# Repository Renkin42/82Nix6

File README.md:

# 82Nix6
An open hardware Nixie Tube Internet Radio alarm clock.

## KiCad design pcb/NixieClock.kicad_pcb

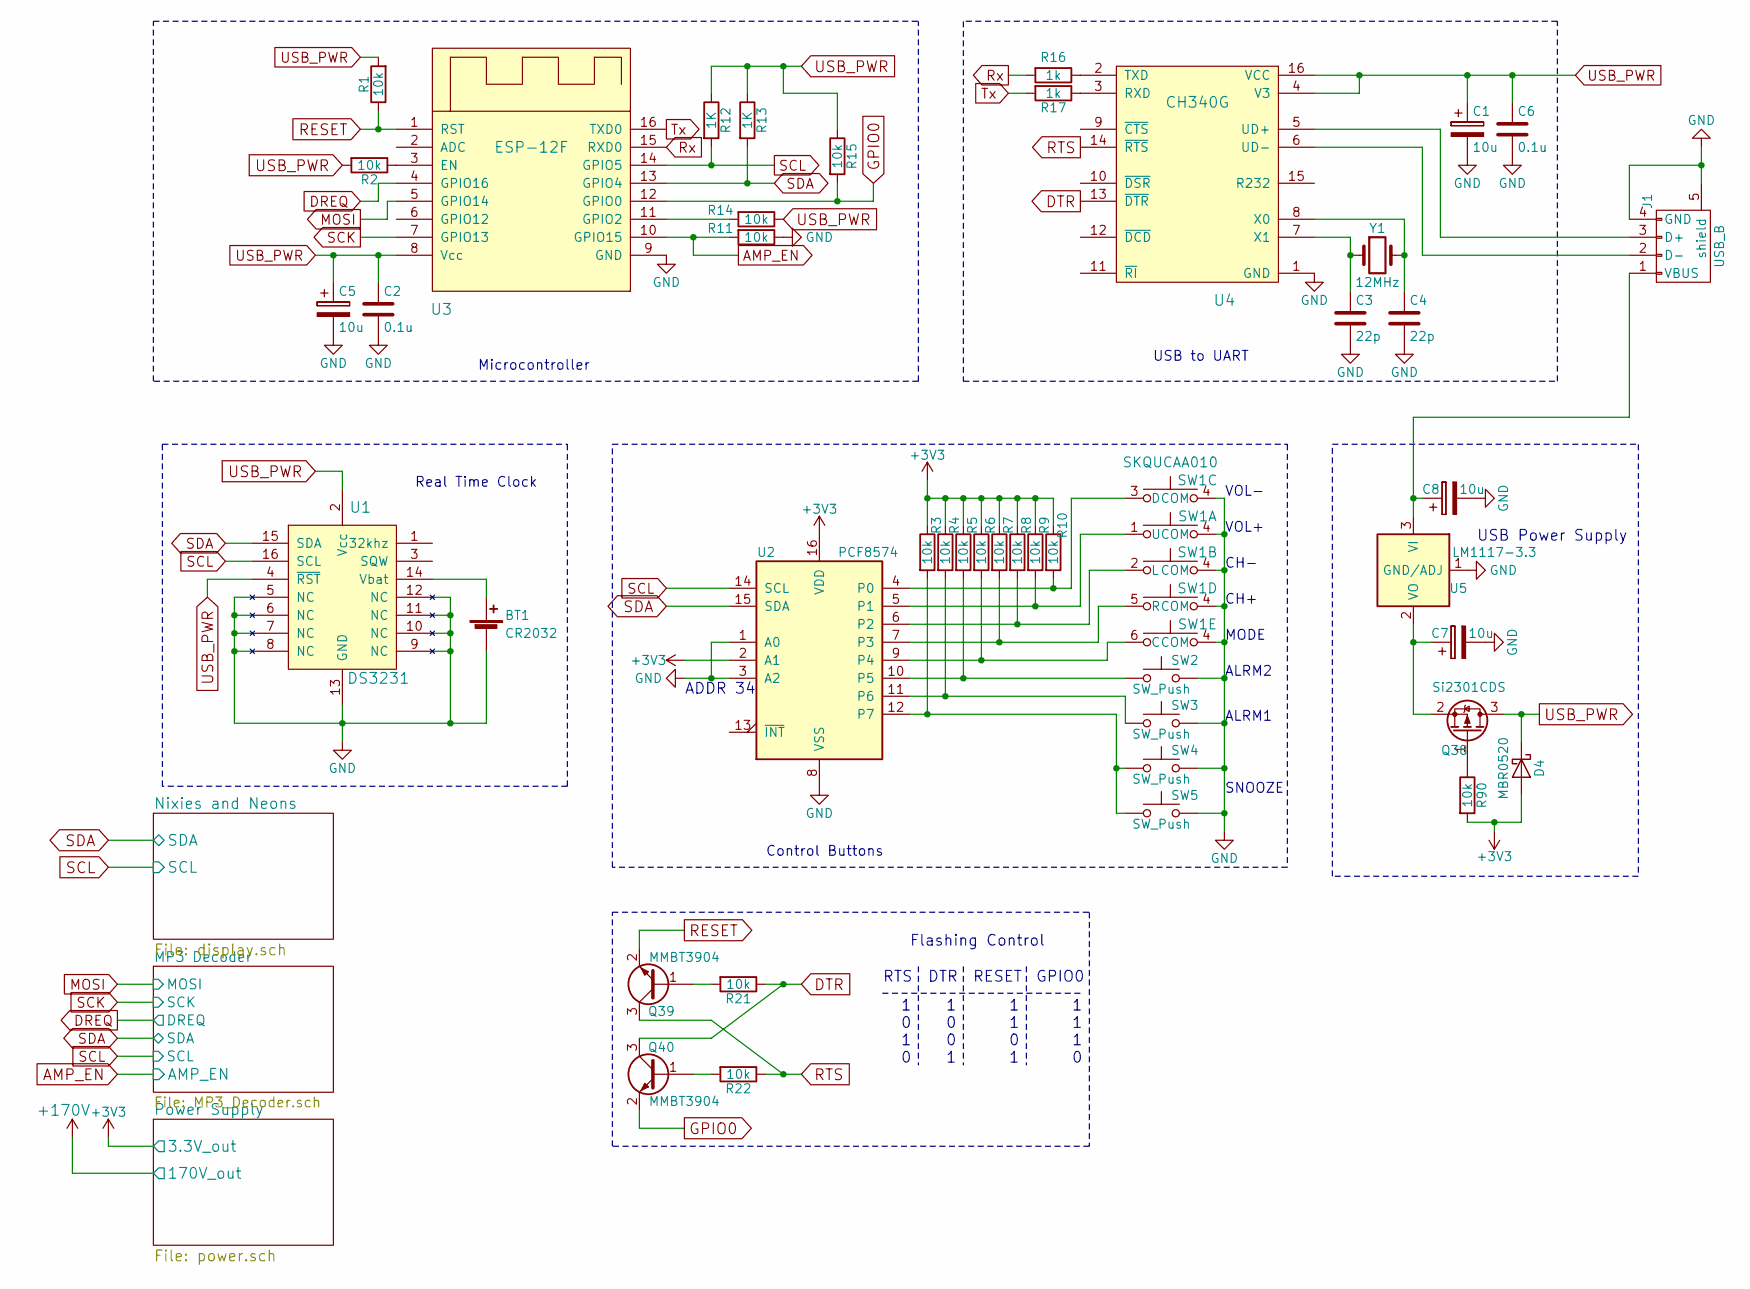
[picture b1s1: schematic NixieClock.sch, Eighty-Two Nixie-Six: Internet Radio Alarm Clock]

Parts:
BT1: CR2032; Linx_Battery_Holder
C1, C5, C7, C8: 10u; CP_Tantalum_Case-A_EIA-3216-18_Hand
C2, C6: 0.1u; C_0805_HandSoldering
C3, C4: 22p; C_0805_HandSoldering
D4: MBR0520; D_SOD-123
J1: USB_B
Q38: Si2301CDS; SOT-23_Handsoldering
Q39, Q40: MMBT3904; SOT-23_Handsoldering
R1, R2, R3, R4, R5, R6, R7, R8, R9, R10, R11, R14, R15, R21, R22, R90: 10k; R_0805_HandSoldering
R12, R13: 1K; R_0805_HandSoldering
R16, R17: 1k; R_0805_HandSoldering
SW1: SKQUCAA010
SW2, SW3: SW_Push; SW_PUSH_6mm
SW4, SW5: SW_Push; SW_Tactile_SKHH_Angled
U1: DS3231; SOIC-16W_7.5x10.3mm_Pitch1.27mm
U2: PCF8574; SOIC-16W_7.5x10.3mm_Pitch1.27mm
U3: ESP-12F; ESP_SMD_Module
U4: CH340G; SOIC-16_3.9x9.9mm_Pitch1.27mm
U5: LM1117-3.3; SOT-223
Y1: 12MHz; Crystal_HC49-4H_Vertical

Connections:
+3V3: D4.2 (A), R3.1, R4.1, R5.1, R6.1, R7.1, R8.1, R9.1, R10.1, R90.2, U2.2 (A1), U2.16 (VDD); also elsewhere on the board
AMP_EN: R11.2, U3.10 (GPIO15); also elsewhere on the board
DREQ: U3.4 (GPIO16); also elsewhere on the board
DTR: Q40.3 (C), R21.1, U4.13 (~DTR)
GND: BT1.2 (-), C1.2, C2.2, C3.2, C4.2, C5.2, C6.2, C7.2, C8.2, J1.4 (GND), J1.5 (shield), R11.1, SW1.4 (COM), SW2.2, SW3.2, SW4.2, SW5.2, U1.5 (NC), U1.6 (NC), U1.7 (NC), U1.8 (NC), U1.9 (NC), U1.10 (NC), U1.11 (NC), U1.12 (NC), U1.13 (GND), U2.1 (A0), U2.3 (A2), U2.8 (VSS), U3.9 (GND), U4.1 (GND), U5.1 (GND/ADJ); also elsewhere on the board
GPIO0: Q40.2 (E), R15.2, U3.12 (GPIO0)
MOSI: U3.5 (GPIO14); also elsewhere on the board
unnamed: BT1.1 (+), U1.14 (Vbat)
unnamed: C3.1, U4.7 (X1), Y1.1
unnamed: C4.1, U4.8 (X0), Y1.2
unnamed: C7.1, Q38.2 (S), U5.2 (VO), U5.4 (VO)
unnamed: C8.1, J1.1 (VBUS), U5.3 (VI)
unnamed: J1.2 (D-), U4.6 (UD-)
unnamed: J1.3 (D+), U4.5 (UD+)
unnamed: Q38.1 (G), R90.1
unnamed: Q39.1 (B), R21.2
unnamed: Q40.1 (B), R22.2
unnamed: R2.1, U3.3 (EN)
unnamed: R3.2, SW4.1, SW5.1, U2.12 (P7)
unnamed: R4.2, SW3.1, U2.11 (P6)
unnamed: R5.2, SW2.1, U2.10 (P5)
unnamed: R6.2, SW1.6 (C), U2.9 (P4)
unnamed: R7.2, SW1.5 (R), U2.7 (P3)
unnamed: R8.2, SW1.2 (L), U2.6 (P2)
unnamed: R9.2, SW1.1 (U), U2.5 (P1)
unnamed: R10.2, SW1.3 (D), U2.4 (P0)
unnamed: R14.2, U3.11 (GPIO2)
unnamed: R16.1, U4.2 (TXD)
unnamed: R17.1, U4.3 (RXD)
RESET: Q39.2 (E), R1.1, U3.1 (RST)
RTS: Q39.3 (C), R22.1, U4.14 (~RTS)
Rx: R16.2, U3.15 (RXD0)
SCK: U3.7 (GPIO13); also elsewhere on the board
SCL: R12.2, U1.16 (SCL), U2.14 (SCL), U3.14 (GPIO5); also elsewhere on the board
SDA: R13.2, U1.15 (SDA), U2.15 (SDA), U3.13 (GPIO4); also elsewhere on the board
Tx: R17.2, U3.16 (TXD0)
USB_PWR: C1.1, C2.1, C5.1, C6.1, D4.1 (K), Q38.3 (D), R1.2, R2.2, R12.1, R13.1, R14.1, R15.1, U1.2 (Vcc), U1.4 (~RST), U3.8 (Vcc), U4.4 (V3), U4.16 (VCC)

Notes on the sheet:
ADDR 34
Microcontroller
Control Buttons
VOL+
VOL-
CH-
CH+
MODE
ALRM1
ALRM2
SNOOZE
Real Time Clock
USB to UART
USB Power Supply
RTS
DTR
RESET
GPIO0
1 0 1 0
1 0 0 1
1 1 0 1
1 1 1 0
Flashing Control

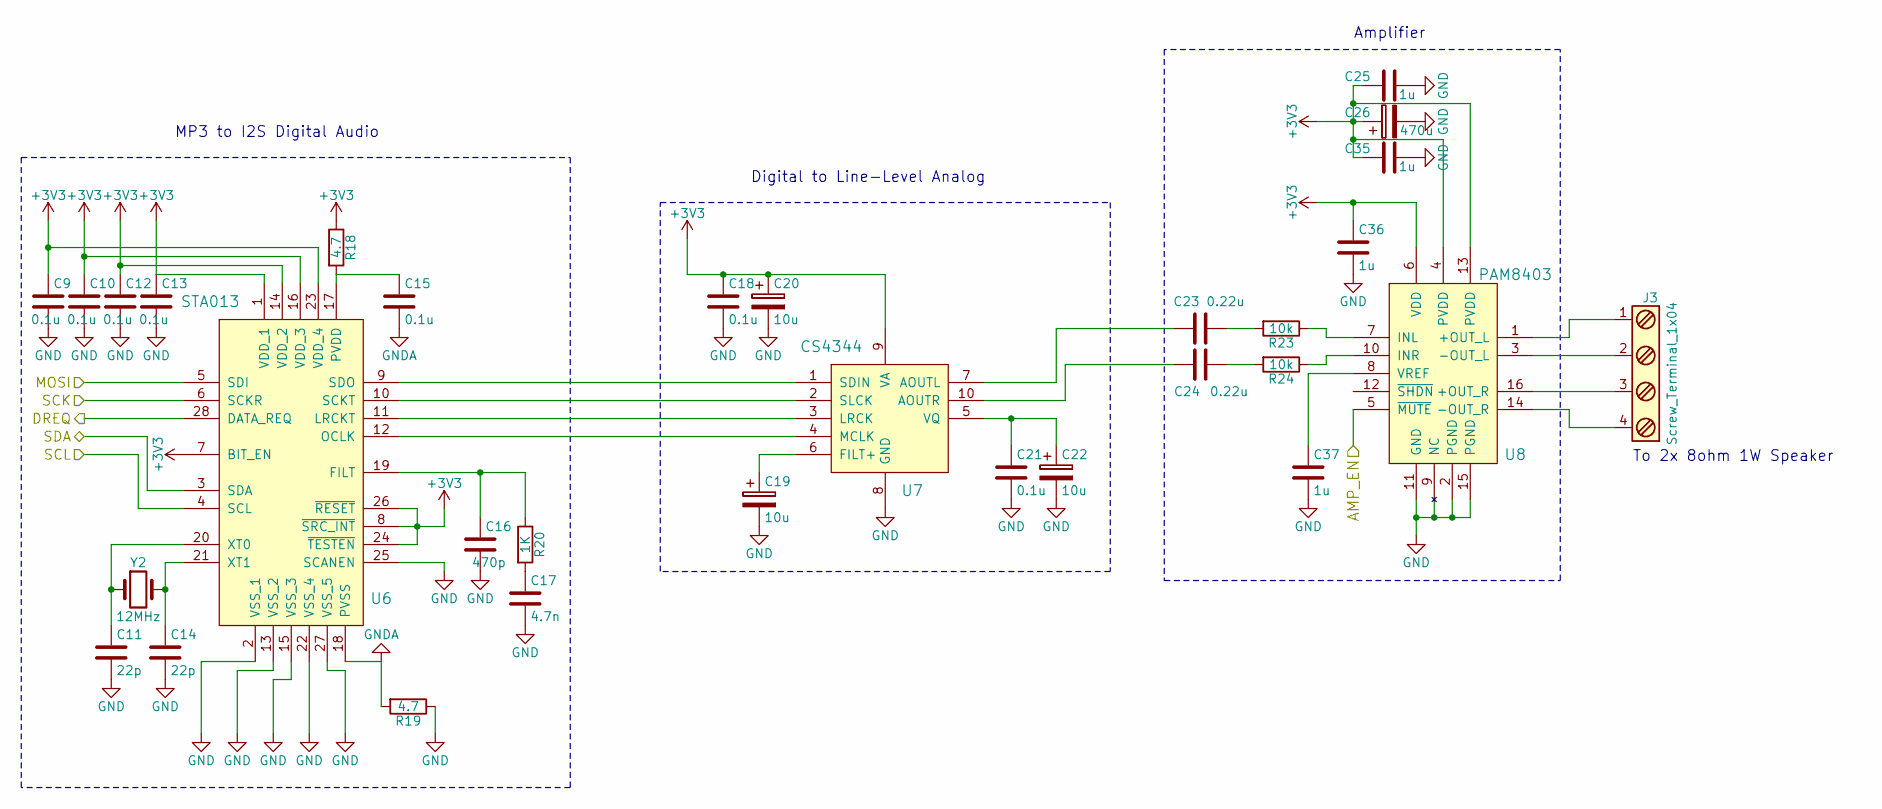
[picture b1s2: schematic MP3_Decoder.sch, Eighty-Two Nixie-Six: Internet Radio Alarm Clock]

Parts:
C9, C10, C12, C13, C15, C18, C21: 0.1u; C_0805_HandSoldering
C11, C14: 22p; C_0805_HandSoldering
C16: 470p; C_0805_HandSoldering
C17: 4.7n; C_0805_HandSoldering
C19, C20, C22: 10u; CP_Tantalum_Case-A_EIA-3216-18_Hand
C23, C24: 0.22u; C_0805_HandSoldering
C25, C35, C36, C37: 1u; C_0805_HandSoldering
C26: 470u; CP_Radial_D6.3mm_P2.50mm
J3: Screw_Terminal_1x04; TerminalBlock_Pheonix_MPT-2.54mm_4pol
R18, R19: 4.7; R_0805_HandSoldering
R20: 1K; R_0805_HandSoldering
R23, R24: 10k; R_0805_HandSoldering
U6: STA013; SOIC-28W_7.5x17.9mm_Pitch1.27mm
U7: CS4344; MSOP-10_3x3mm_Pitch0.5mm
U8: PAM8403; SOIC-16_3.9x9.9mm_Pitch1.27mm
Y2: 12MHz; Crystal_HC49-4H_Vertical

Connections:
+3V3: C9.1, C10.1, C12.1, C13.1, C18.1, C20.1, C25.1, C26.1, C35.1, C36.1, R18.1, U6.1 (VDD_1), U6.7 (BIT_EN), U6.8 (~SRC_INT), U6.14 (VDD_2), U6.16 (VDD_3), U6.23 (VDD_4), U6.24 (~TESTEN), U6.26 (~RESET), U7.9 (VA), U8.4 (PVDD), U8.6 (VDD), U8.13 (PVDD); also elsewhere on the board
AMP_EN: U8.5 (~MUTE); also elsewhere on the board
DREQ: U6.28 (DATA_REQ); also elsewhere on the board
GND: C9.2, C10.2, C11.2, C12.2, C13.2, C14.2, C16.2, C17.2, C18.2, C19.2, C20.2, C21.2, C22.2, C25.2, C26.2, C35.2, C36.2, C37.2, R19.1, U6.2 (VSS_1), U6.13 (VSS_2), U6.15 (VSS_3), U6.22 (VSS_4), U6.25 (SCANEN), U6.27 (VSS_5), U7.8 (GND), U8.2 (PGND), U8.9 (NC), U8.11 (GND), U8.15 (PGND); also elsewhere on the board
GNDA: C15.2, R19.2, U6.18 (PVSS)
MOSI: U6.5 (SDI); also elsewhere on the board
unnamed: C11.1, U6.20 (XT0), Y2.1
unnamed: C14.1, U6.21 (XT1), Y2.2
unnamed: C15.1, R18.2, U6.17 (PVDD)
unnamed: C16.1, R20.1, U6.19 (FILT)
unnamed: C17.1, R20.2
unnamed: C19.1, U7.6 (FILT+)
unnamed: C21.1, C22.1, U7.5 (VQ)
unnamed: C23.1, U7.7 (AOUTL)
unnamed: C23.2, R23.2
unnamed: C24.1, R24.2
unnamed: C24.2, U7.10 (AOUTR)
unnamed: C37.1, U8.8 (VREF)
unnamed: J3.1, U8.1 (+OUT_L)
unnamed: J3.2, U8.3 (-OUT_L)
unnamed: J3.3, U8.16 (+OUT_R)
unnamed: J3.4, U8.14 (-OUT_R)
unnamed: R23.1, U8.7 (INL)
unnamed: R24.1, U8.10 (INR)
unnamed: U6.9 (SDO), U7.1 (SDIN)
unnamed: U6.10 (SCKT), U7.2 (SLCK)
unnamed: U6.11 (LRCKT), U7.3 (LRCK)
unnamed: U6.12 (OCLK), U7.4 (MCLK)
SCK: U6.6 (SCKR); also elsewhere on the board
SCL: U6.4 (SCL); also elsewhere on the board
SDA: U6.3 (SDA); also elsewhere on the board

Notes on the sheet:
MP3 to I2S Digital Audio
Digital to Line-Level Analog
Amplifier
To 2x 8ohm 1W Speaker

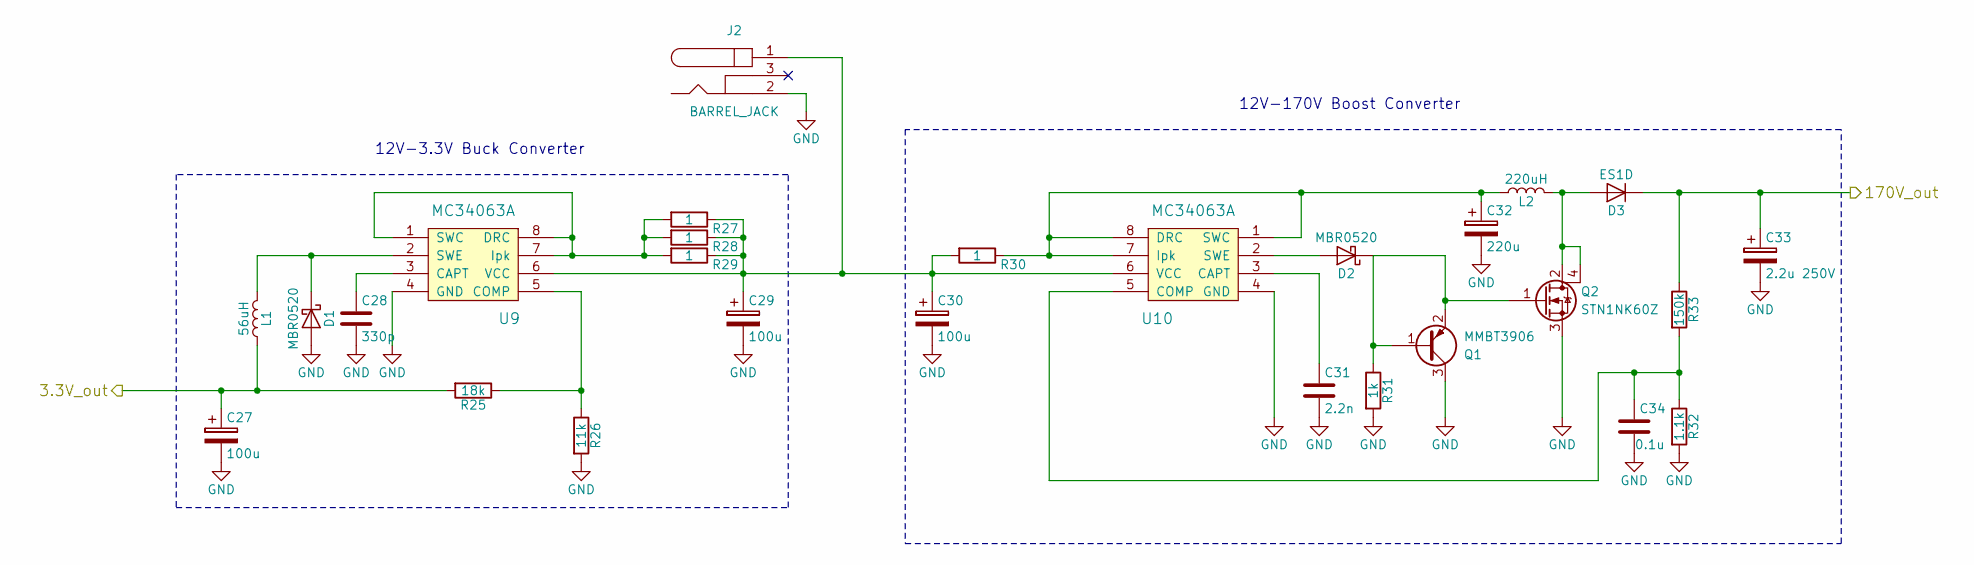
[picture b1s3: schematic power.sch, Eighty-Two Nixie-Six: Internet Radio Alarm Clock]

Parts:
C27, C29, C30: 100u; CP_Radial_D5.0mm_P2.50mm
C28: 330p; C_0805_HandSoldering
C31: 2.2n; C_0805_HandSoldering
C32: 220u; CP_Radial_D6.3mm_P2.50mm
C33: 2.2u 250V; CP_Radial_D6.3mm_P2.50mm
C34: 0.1u; C_0805_HandSoldering
D1, D2: MBR0520; D_SOD-123
D3: ES1D; D_SOD-123
J2: BARREL_JACK
L1: 56uH; Bourns_RLB9012
L2: 220uH; Bourns_RLB0914
Q1: MMBT3906; SOT-23_Handsoldering
Q2: STN1NK60Z; SOT-223
R25: 18k; R_1206_HandSoldering
R26: 11k; R_1206_HandSoldering
R27, R28, R29, R30: 1; R_0805_HandSoldering
R31: 1k; R_0805_HandSoldering
R32: 1.1k; R_1206_HandSoldering
R33: 150k; R_1206_HandSoldering
U9, U10: MC34063A; SOIC-8_3.9x4.9mm_Pitch1.27mm

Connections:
+3V3: C27.1, L1.2, R25.2; also elsewhere on the board
+170V: C33.1, D3.1 (K), R33.1; also elsewhere on the board
GND: C27.2, C28.2, C29.2, C30.2, C31.2, C32.2, C33.2, C34.2, D1.2 (A), J2.2, Q1.3 (C), Q2.3 (S), R26.2, R31.2, R32.2, U9.4 (GND), U10.4 (GND); also elsewhere on the board
unnamed: C28.1, U9.3 (CAPT)
unnamed: C29.1, C30.1, J2.1, R27.1, R28.1, R29.1, R30.2, U9.6 (VCC), U10.6 (VCC)
unnamed: C31.1, U10.3 (CAPT)
unnamed: C32.1, L2.2, R30.1, U10.1 (SWC), U10.7 (Ipk), U10.8 (DRC)
unnamed: C34.1, R32.1, R33.2, U10.5 (COMP)
unnamed: D1.1 (K), L1.1, U9.2 (SWE)
unnamed: D2.1 (K), Q1.1 (B), Q1.2 (E), Q2.1 (G), R31.1
unnamed: D2.2 (A), U10.2 (SWE)
unnamed: D3.2 (A), L2.1, Q2.2 (D), Q2.4 (D)
unnamed: R25.1, R26.1, U9.5 (COMP)
unnamed: R27.2, R28.2, R29.2, U9.1 (SWC), U9.7 (Ipk), U9.8 (DRC)

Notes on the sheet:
12V-170V Boost Converter
12V-3.3V Buck Converter

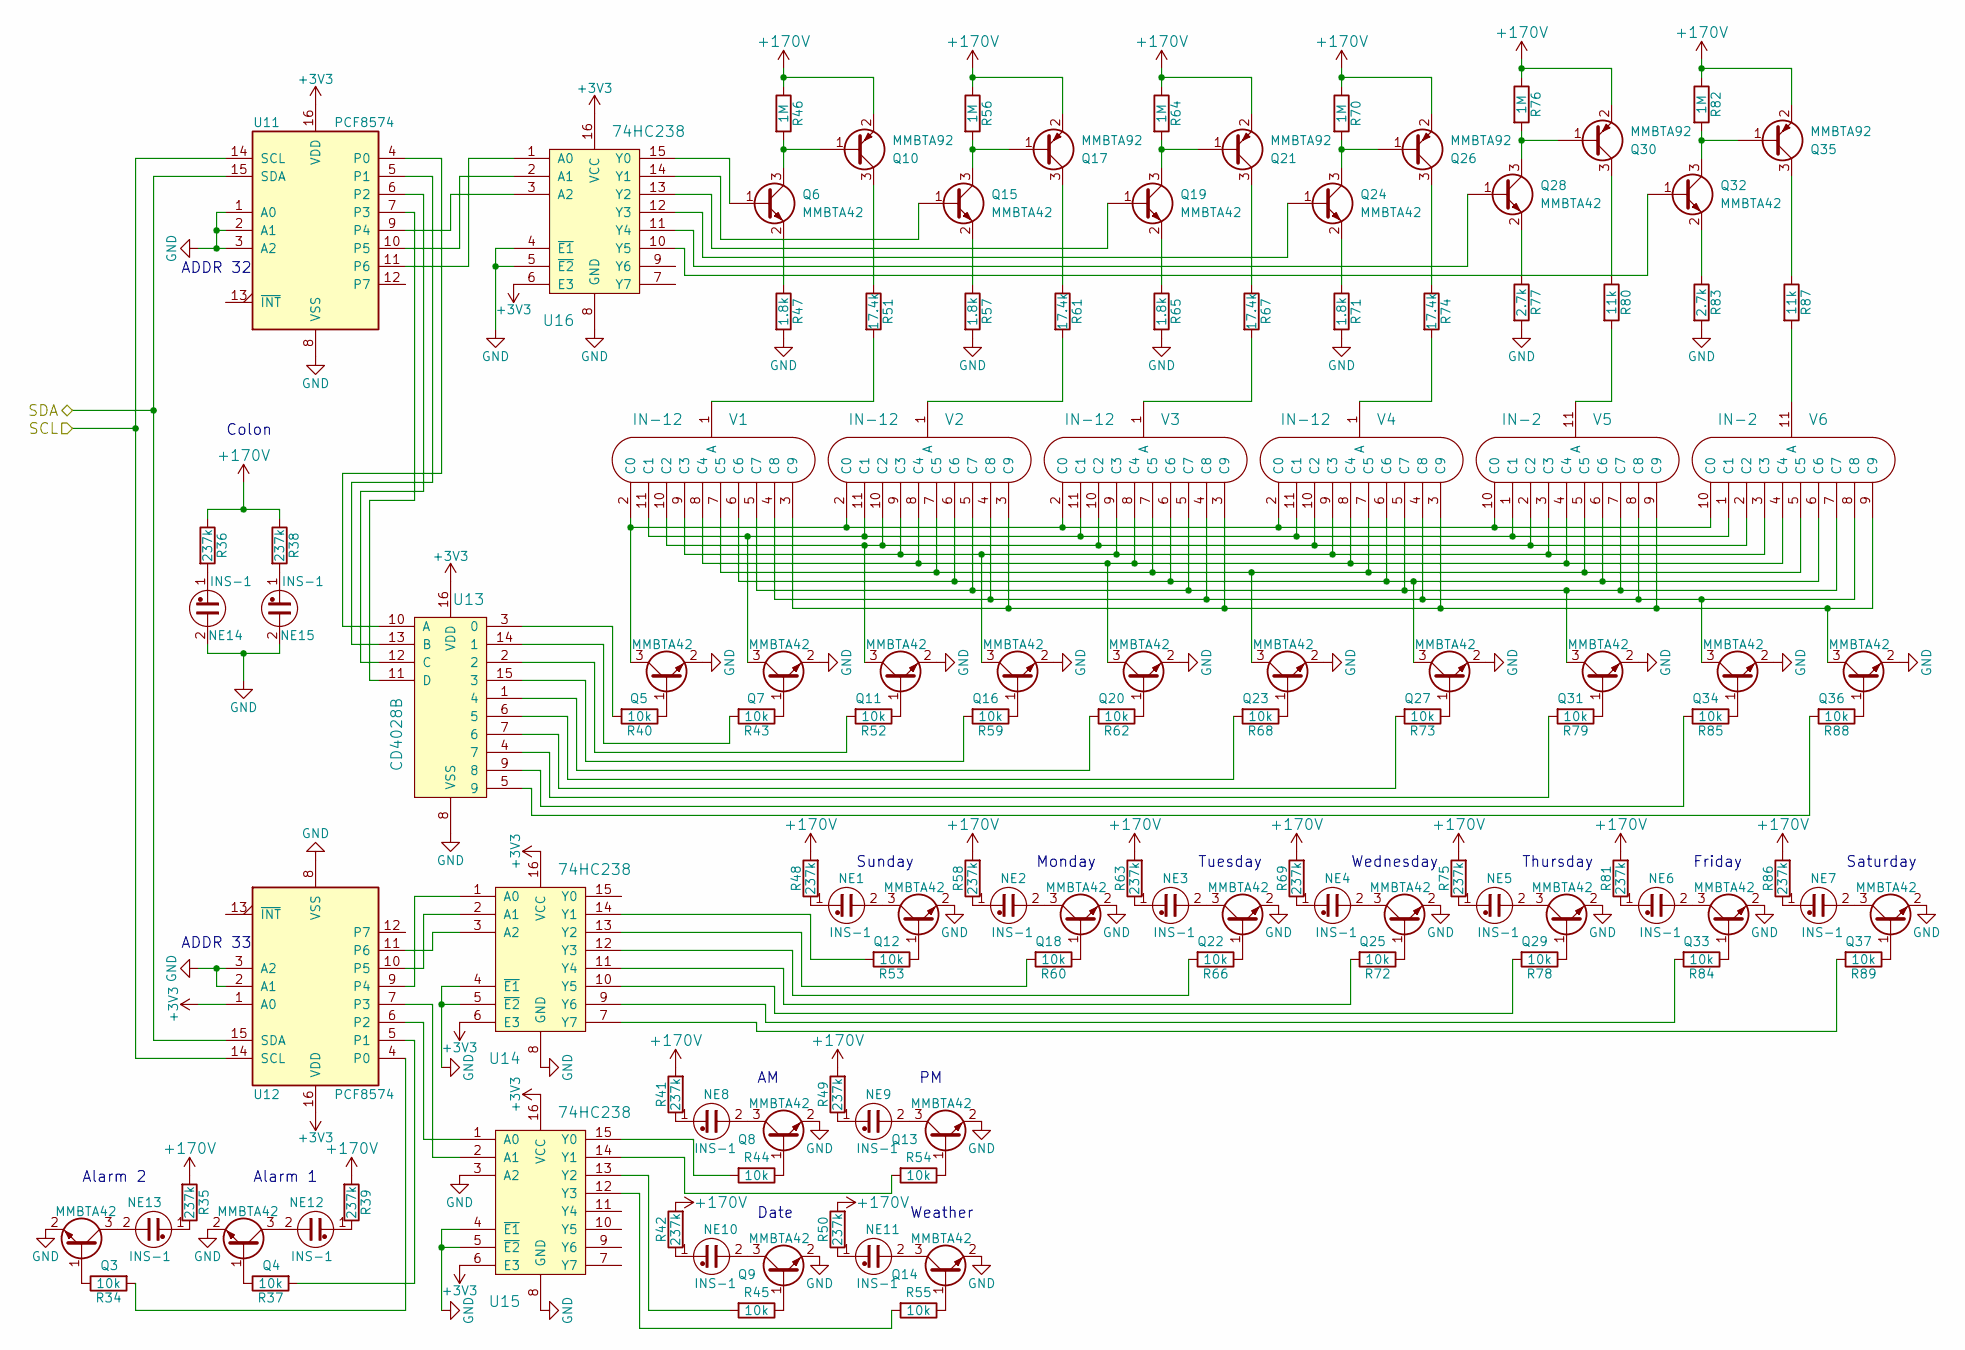
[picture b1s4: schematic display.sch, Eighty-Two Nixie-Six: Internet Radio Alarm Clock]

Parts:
NE1, NE2, NE3, NE4, NE5, NE6, NE7, NE8, NE9, NE10, NE11, NE12, NE13, NE14, NE15: INS-1
Q3, Q4, Q5, Q6, Q7, Q8, Q9, Q11, Q12, Q13, Q14, Q15, Q16, Q18, Q19, Q20, Q22, Q23, Q24, Q25, Q27, Q28, Q29, Q31, Q32, Q33, Q34, Q36, Q37: MMBTA42; SOT-23_Handsoldering
Q10, Q17, Q21, Q26, Q30, Q35: MMBTA92; SOT-23_Handsoldering
R34, R37, R40, R43, R44, R45, R52, R53, R54, R55, R59, R60, R62, R66, R68, R72, R73, R78, R79, R84, R85, R88, R89: 10k; R_0805_HandSoldering
R35, R36, R38, R39, R41, R42, R48, R49, R50, R58, R63, R69, R75, R81, R86: 237k; R_1206_HandSoldering
R46, R56, R64, R70, R76, R82: 1M; R_1206_HandSoldering
R47, R57, R65, R71: 1.8k; R_1206_HandSoldering
R51, R61, R67, R74: 17.4k; R_1206_HandSoldering
R77, R83: 2.7k; R_1206_HandSoldering
R80, R87: 11k; R_1206_HandSoldering
U11, U12: PCF8574; SOIC-18W_7.5x11.6mm_Pitch1.27mm
U13: CD4028B; SOIC-16_3.9x9.9mm_Pitch1.27mm
U14, U15, U16: 74HC238; SOIC-16_3.9x9.9mm_Pitch1.27mm
V1, V2, V3, V4: IN-12
V5, V6: IN-2

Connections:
+3V3: U11.16 (VDD), U12.1 (A0), U12.16 (VDD), U13.16 (VDD), U14.6 (E3), U14.16 (VCC), U15.6 (E3), U15.16 (VCC), U16.6 (E3), U16.16 (VCC); also elsewhere on the board
+170V: Q10.2 (E), Q17.2 (E), Q21.2 (E), Q26.2 (E), Q30.2 (E), Q35.2 (E), R35.2, R36.1, R38.1, R39.2, R41.2, R42.2, R46.1, R48.2, R49.2, R50.2, R56.1, R58.2, R63.2, R64.1, R69.2, R70.1, R75.2, R76.1, R81.2, R82.1, R86.2; also elsewhere on the board
GND: NE14.2, NE15.2, Q3.2 (E), Q4.2 (E), Q5.2 (E), Q7.2 (E), Q8.2 (E), Q9.2 (E), Q11.2 (E), Q12.2 (E), Q13.2 (E), Q14.2 (E), Q16.2 (E), Q18.2 (E), Q20.2 (E), Q22.2 (E), Q23.2 (E), Q25.2 (E), Q27.2 (E), Q29.2 (E), Q31.2 (E), Q33.2 (E), Q34.2 (E), Q36.2 (E), Q37.2 (E), R47.2, R57.2, R65.2, R71.2, R77.2, R83.2, U11.1 (A0), U11.2 (A1), U11.3 (A2), U11.8 (VSS), U12.2 (A1), U12.3 (A2), U12.8 (VSS), U13.8 (VSS), U14.4 (~E1), U14.5 (~E2), U14.8 (GND), U15.3 (A2), U15.4 (~E1), U15.5 (~E2), U15.8 (GND), U16.4 (~E1), U16.5 (~E2), U16.8 (GND); also elsewhere on the board
unnamed: NE1.1, R48.1
unnamed: NE1.2, Q12.3 (C)
unnamed: NE2.1, R58.1
unnamed: NE2.2, Q18.3 (C)
unnamed: NE3.1, R63.1
unnamed: NE3.2, Q22.3 (C)
unnamed: NE4.1, R69.1
unnamed: NE4.2, Q25.3 (C)
unnamed: NE5.1, R75.1
unnamed: NE5.2, Q29.3 (C)
unnamed: NE6.1, R81.1
unnamed: NE6.2, Q33.3 (C)
unnamed: NE7.1, R86.1
unnamed: NE7.2, Q37.3 (C)
unnamed: NE8.1, R41.1
unnamed: NE8.2, Q8.3 (C)
unnamed: NE9.1, R49.1
unnamed: NE9.2, Q13.3 (C)
unnamed: NE10.1, R42.1
unnamed: NE10.2, Q9.3 (C)
unnamed: NE11.1, R50.1
unnamed: NE11.2, Q14.3 (C)
unnamed: NE12.1, R39.1
unnamed: NE12.2, Q4.3 (C)
unnamed: NE13.1, R35.1
unnamed: NE13.2, Q3.3 (C)
unnamed: NE14.1, R36.2
unnamed: NE15.1, R38.2
unnamed: Q3.1 (B), R34.1
unnamed: Q4.1 (B), R37.1
unnamed: Q5.1 (B), R40.1
unnamed: Q5.3 (C), V1.2 (C0), V2.2 (C0), V3.2 (C0), V4.2 (C0), V5.10 (C0), V6.10 (C0)
unnamed: Q6.1 (B), U16.15 (Y0)
unnamed: Q6.2 (E), R47.1
unnamed: Q7.1 (B), R43.1
unnamed: Q7.3 (C), V1.11 (C1), V2.11 (C1), V3.11 (C1), V4.11 (C1), V5.1 (C1), V6.1 (C1)
unnamed: Q8.1 (B), R44.1
unnamed: Q9.1 (B), R45.1
unnamed: Q6.3 (C), Q10.1 (B), R46.2
unnamed: Q10.3 (C), R51.1
unnamed: Q11.1 (B), R52.1
unnamed: Q11.3 (C), V1.10 (C2), V2.10 (C2), V3.10 (C2), V4.10 (C2), V5.2 (C2), V6.2 (C2)
unnamed: Q12.1 (B), R53.1
unnamed: Q13.1 (B), R54.1
unnamed: Q14.1 (B), R55.1
unnamed: Q15.1 (B), U16.14 (Y1)
unnamed: Q15.2 (E), R57.1
unnamed: Q15.3 (C), Q17.1 (B), R56.2
unnamed: Q16.1 (B), R59.1
unnamed: Q16.3 (C), V1.9 (C3), V2.9 (C3), V3.9 (C3), V4.9 (C3), V5.3 (C3), V6.3 (C3)
unnamed: Q17.3 (C), R61.1
unnamed: Q18.1 (B), R60.1
unnamed: Q19.1 (B), U16.13 (Y2)
unnamed: Q19.2 (E), R65.1
unnamed: Q19.3 (C), Q21.1 (B), R64.2
unnamed: Q20.1 (B), R62.1
unnamed: Q20.3 (C), V1.8 (C4), V2.8 (C4), V3.8 (C4), V4.8 (C4), V5.4 (C4), V6.4 (C4)
unnamed: Q21.3 (C), R67.1
unnamed: Q22.1 (B), R66.1
unnamed: Q23.1 (B), R68.1
unnamed: Q23.3 (C), V1.7 (C5), V2.7 (C5), V3.7 (C5), V4.7 (C5), V5.5 (C5), V6.5 (C5)
unnamed: Q24.1 (B), U16.12 (Y3)
unnamed: Q24.2 (E), R71.1
unnamed: Q24.3 (C), Q26.1 (B), R70.2
unnamed: Q25.1 (B), R72.1
unnamed: Q26.3 (C), R74.1
unnamed: Q27.1 (B), R73.1
unnamed: Q27.3 (C), V1.6 (C6), V2.6 (C6), V3.6 (C6), V4.6 (C6), V5.6 (C6), V6.6 (C6)
unnamed: Q28.1 (B), U16.11 (Y4)
unnamed: Q28.2 (E), R77.1
unnamed: Q28.3 (C), Q30.1 (B), R76.2
unnamed: Q29.1 (B), R78.1
unnamed: Q30.3 (C), R80.1
unnamed: Q31.1 (B), R79.1
unnamed: Q31.3 (C), V1.5 (C7), V2.5 (C7), V3.5 (C7), V4.5 (C7), V5.7 (C7), V6.7 (C7)
unnamed: Q32.1 (B), U16.10 (Y5)
unnamed: Q32.2 (E), R83.1
unnamed: Q32.3 (C), Q35.1 (B), R82.2
unnamed: Q33.1 (B), R84.1
unnamed: Q34.1 (B), R85.1
unnamed: Q34.3 (C), V1.4 (C8), V2.4 (C8), V3.4 (C8), V4.4 (C8), V5.8 (C8), V6.8 (C8)
unnamed: Q35.3 (C), R87.1
unnamed: Q36.1 (B), R88.1
unnamed: Q36.3 (C), V1.3 (C9), V2.3 (C9), V3.3 (C9), V4.3 (C9), V5.9 (C9), V6.9 (C9)
unnamed: Q37.1 (B), R89.1
unnamed: R34.2, U12.4 (P0)
unnamed: R37.2, U12.5 (P1)
unnamed: R40.2, U13.3 (0)
unnamed: R43.2, U13.14 (1)
unnamed: R44.2, U15.15 (Y0)
unnamed: R45.2, U15.13 (Y2)
unnamed: R51.2, V1.1 (A)
unnamed: R52.2, U13.2
unnamed: R53.2, U14.14 (Y1)
unnamed: R54.2, U15.14 (Y1)
unnamed: R55.2, U15.12 (Y3)
unnamed: R59.2, U13.15 (3)
unnamed: R60.2, U14.13 (Y2)
unnamed: R61.2, V2.1 (A)
unnamed: R62.2, U13.1 (4)
unnamed: R66.2, U14.12 (Y3)
unnamed: R67.2, V3.1 (A)
unnamed: R68.2, U13.6 (5)
unnamed: R72.2, U14.11 (Y4)
unnamed: R73.2, U13.7 (6)
unnamed: R74.2, V4.1 (A)
unnamed: R78.2, U14.10 (Y5)
unnamed: R79.2, U13.4 (7)
unnamed: R80.2, V5.11 (A)
unnamed: R84.2, U14.9 (Y6)
unnamed: R85.2, U13.9 (8)
unnamed: R87.2, V6.11 (A)
unnamed: R88.2, U13.5 (9)
unnamed: R89.2, U14.7 (Y7)
unnamed: U11.4 (P0), U13.10 (A)
unnamed: U11.5 (P1), U13.13 (B)
unnamed: U11.6 (P2), U13.12 (C)
unnamed: U11.7 (P3), U13.11 (D)
unnamed: U11.9 (P4), U16.3 (A2)
unnamed: U11.10 (P5), U16.2 (A1)
unnamed: U11.11 (P6), U16.1 (A0)
unnamed: U12.6 (P2), U15.1 (A0)
unnamed: U12.7 (P3), U15.2 (A1)
unnamed: U12.9 (P4), U14.1 (A0)
unnamed: U12.10 (P5), U14.2 (A1)
unnamed: U12.11 (P6), U14.3 (A2)
SCL: U11.14 (SCL), U12.14 (SCL); also elsewhere on the board
SDA: U11.15 (SDA), U12.15 (SDA); also elsewhere on the board

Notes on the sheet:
Sunday
Monday
Tuesday
Wednesday
Thursday
Friday
Saturday
Date
Weather
Alarm 1
Alarm 2
Colon
ADDR 32
ADDR 33

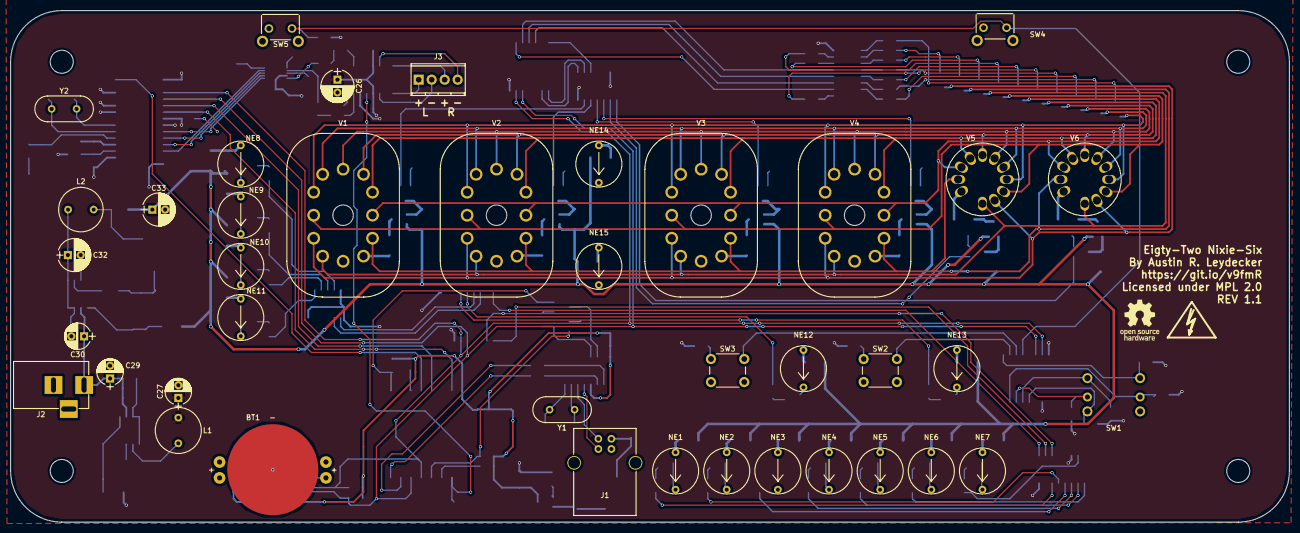
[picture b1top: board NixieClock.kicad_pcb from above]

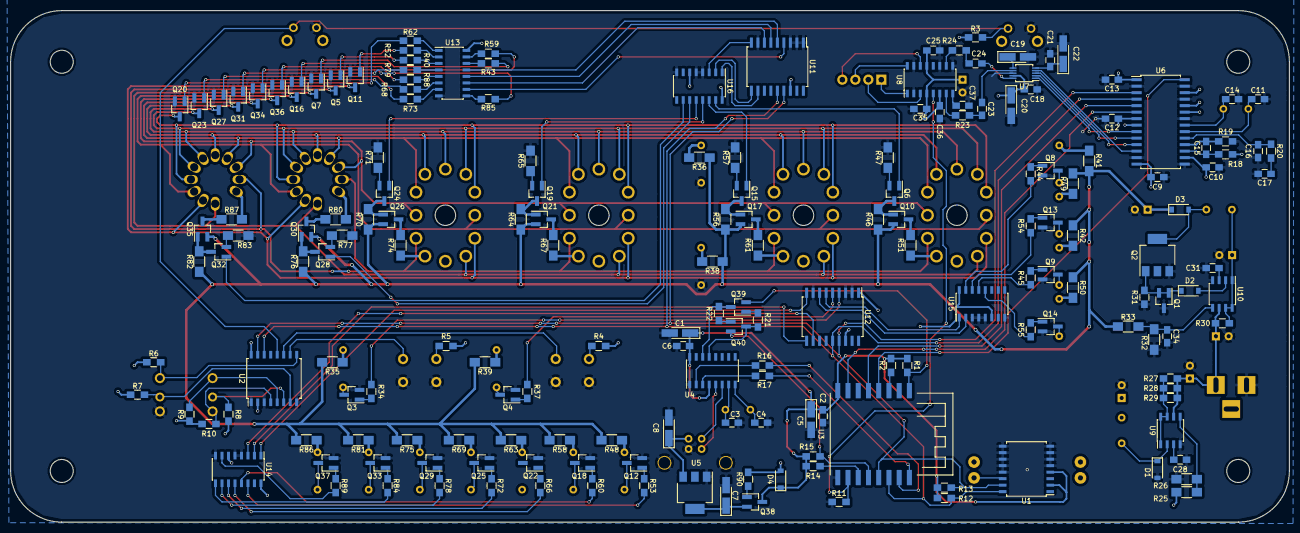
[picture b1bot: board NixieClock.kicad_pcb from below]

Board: 2 copper layers, 250.0 x 100.0 mm, 221 parts (181 on the bottom side), 198 nets.

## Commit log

2017-04-11 Add initial pcb files
2017-04-11 Added notes to speaker output terminal block
2017-04-17 Use RTS and DTR for flashing instead of switch
2017-04-18 Added model for ESP12. Updated schematic exports.
2017-04-21 Switched to nodemcu-style flashing circuitry.
2017-04-21 Swapped Q2 for cheaper STN1NK60Z. Fixed some ground plane issues.

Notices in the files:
pcb/MP3_Decoder.sch:
Licensed under MPL 2.0
